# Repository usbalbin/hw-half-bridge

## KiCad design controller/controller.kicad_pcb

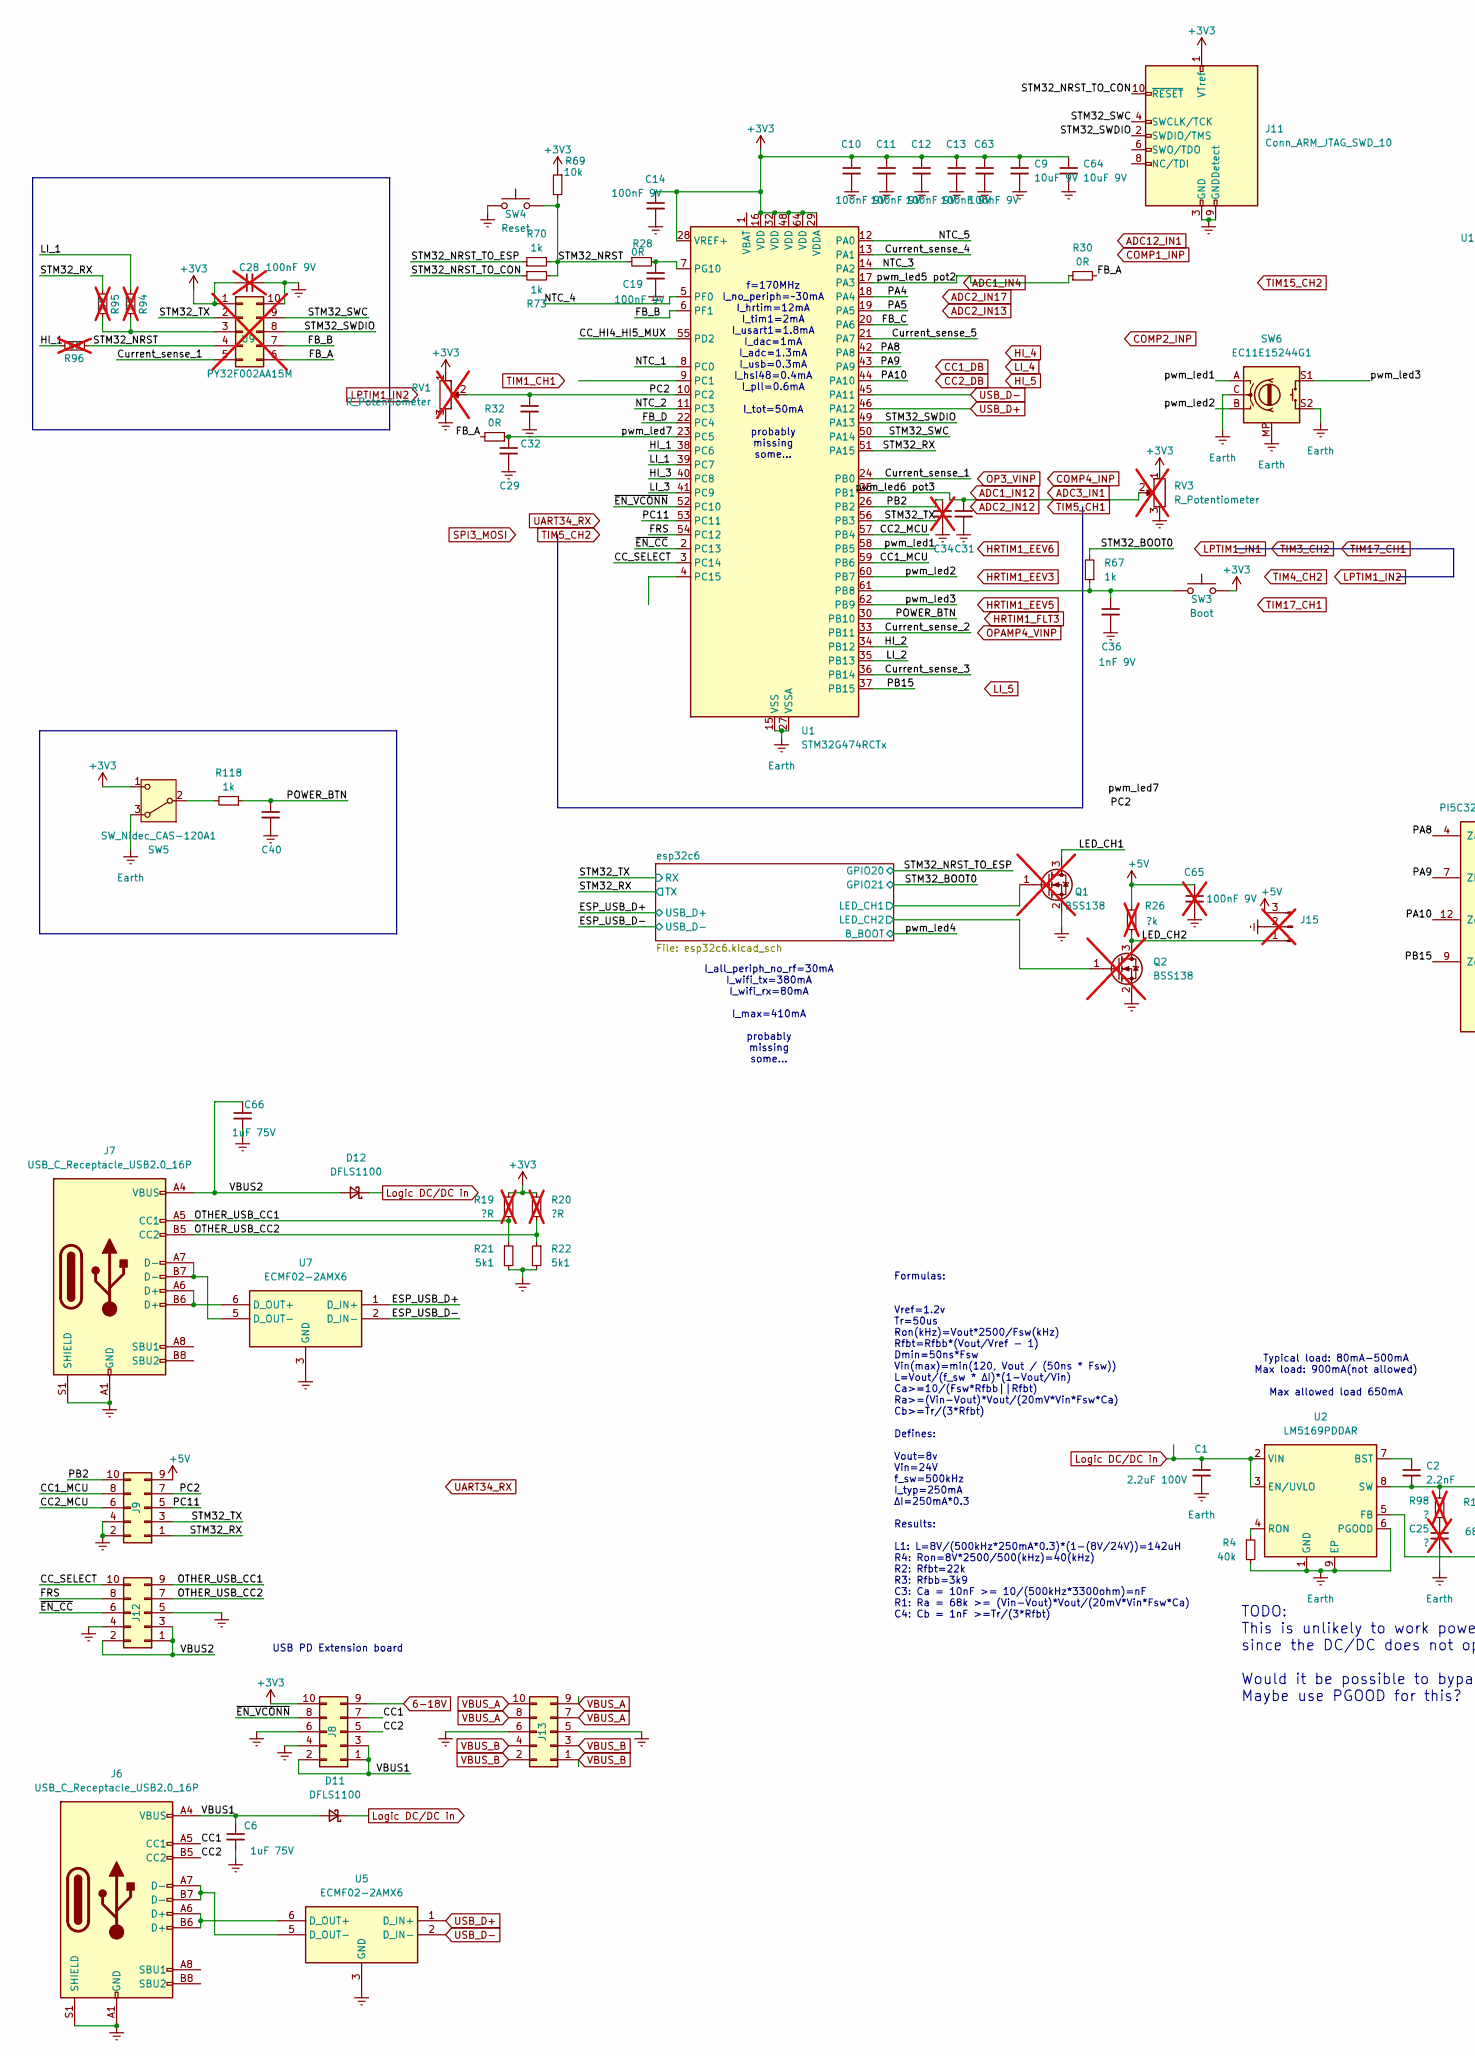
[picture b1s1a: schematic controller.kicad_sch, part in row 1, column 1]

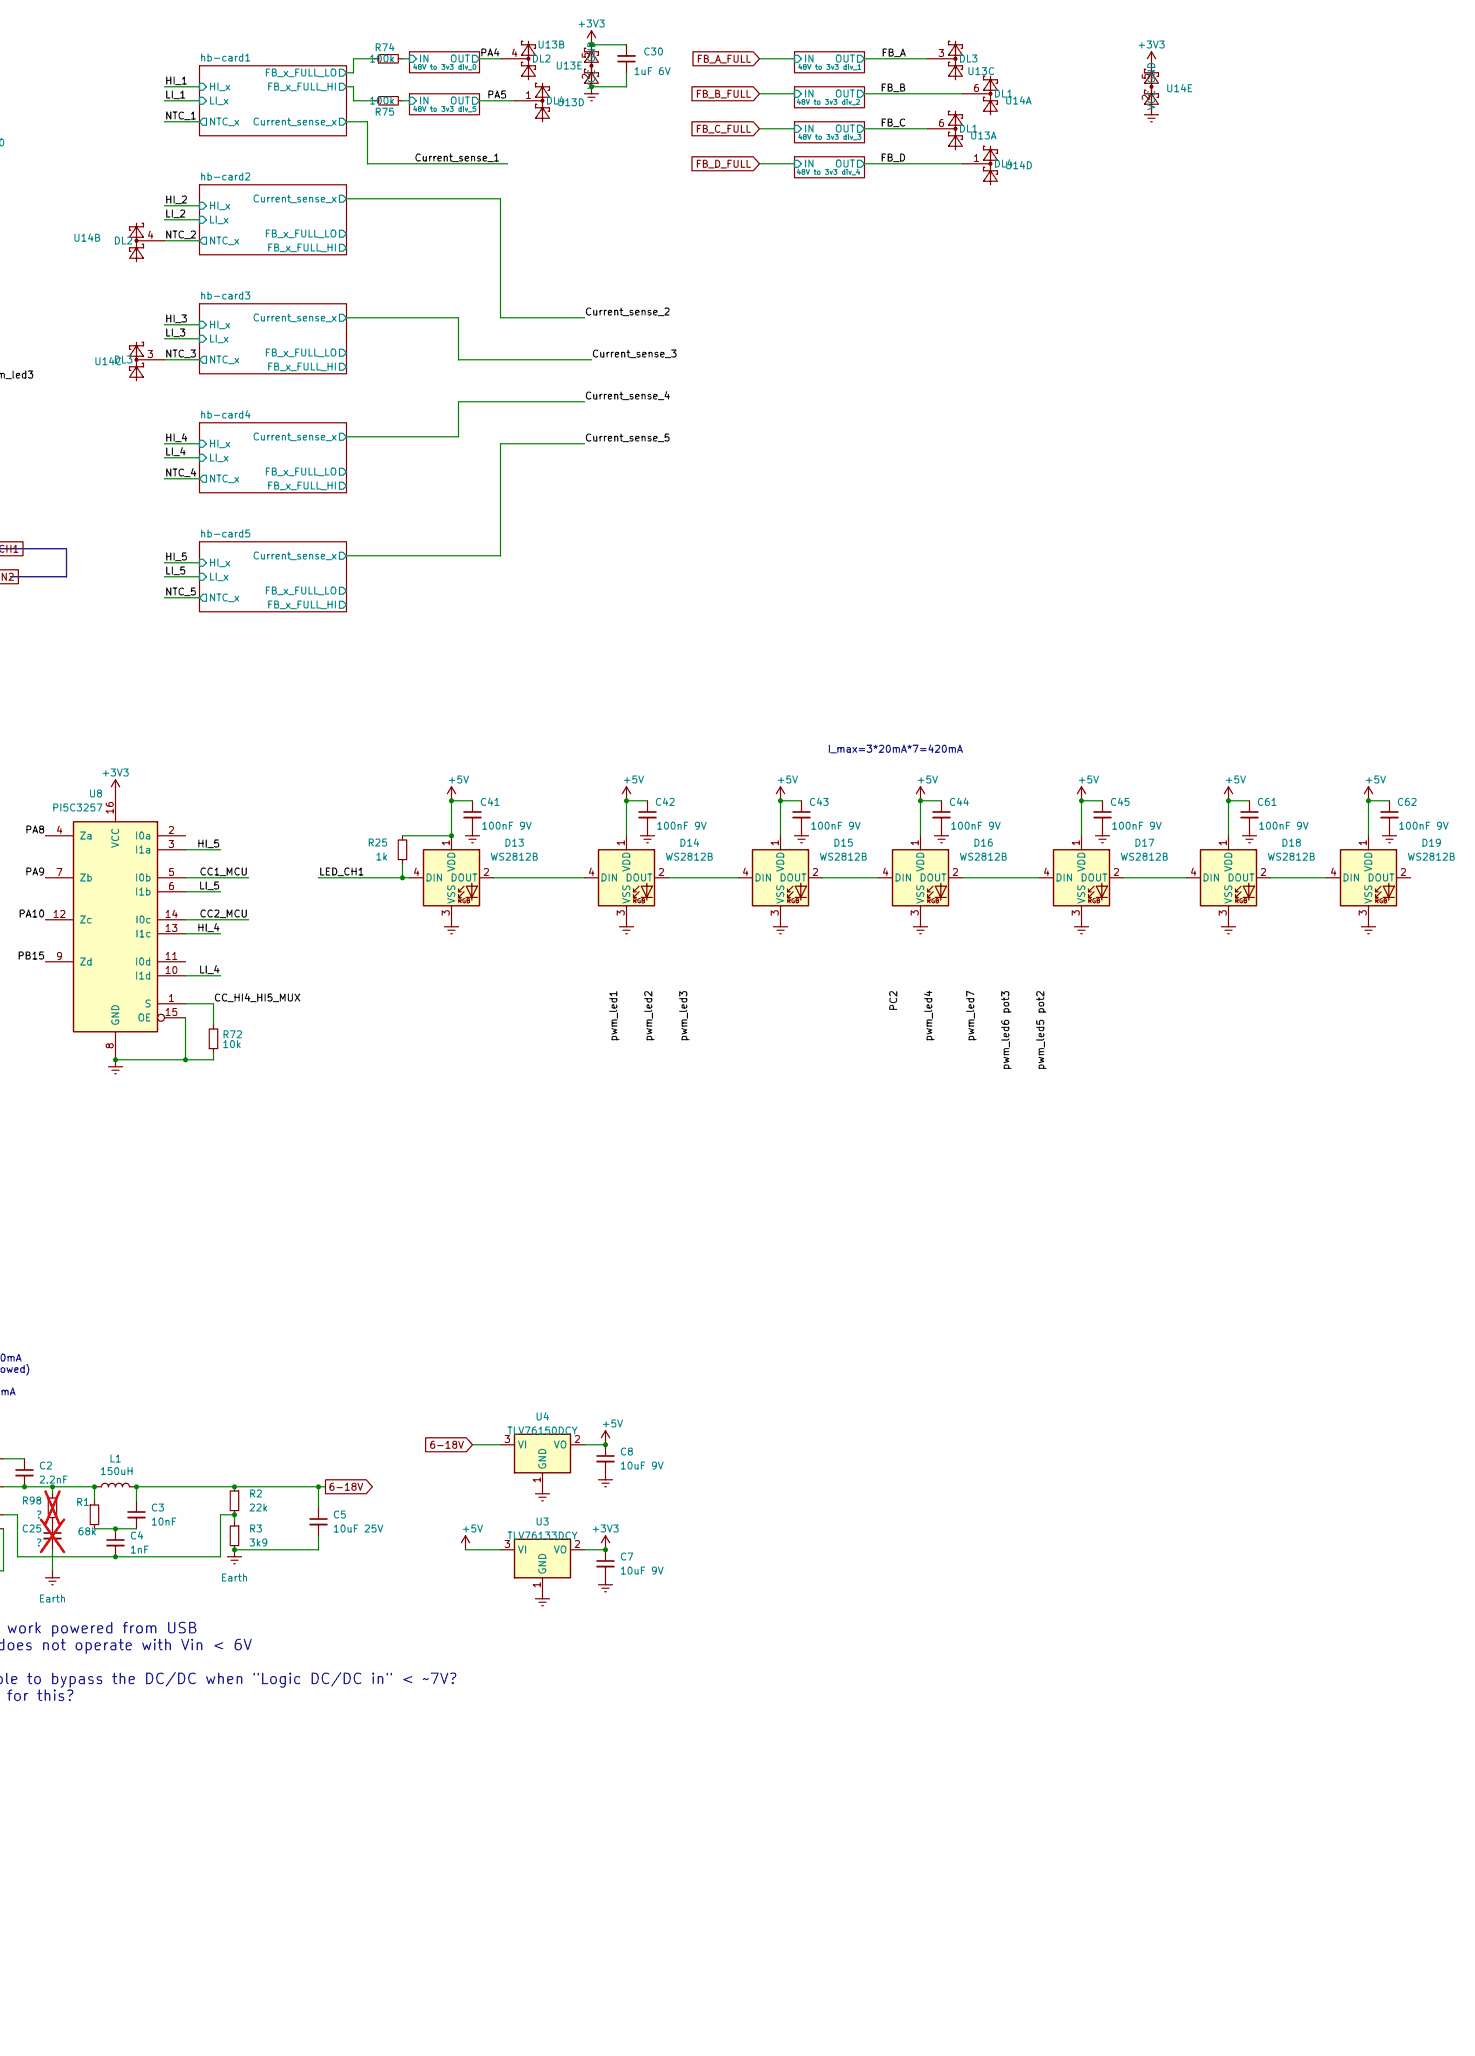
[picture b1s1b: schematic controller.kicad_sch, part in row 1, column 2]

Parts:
C1: 2.2uF 100V; C_1206_3216Metric
C2: 2.2nF; C_0603_1608Metric
C3: 10nF; C_0603_1608Metric
C4: 1nF; C_0603_1608Metric
C5: 10uF 25V; C_1206_3216Metric
C6, C66: 1uF 75V; C_0603_1608Metric
C7, C8, C9, C64: 10uF 9V; C_0805_2012Metric
C10, C11, C12, C13, C14, C19, C29, C31, C32, C40, C41, C42, C43, C44, C45, C61, C62, C63: 100nF 9V; C_0402_1005Metric
C25: ?; C_0603_1608Metric; not fitted
C28, C65: 100nF 9V; C_0402_1005Metric; not fitted
C30: 1uF 6V; C_0402_1005Metric
C34: 10nF 9V; C_0402_1005Metric; not fitted
C36: 1nF 9V; C_0402_1005Metric
D11, D12: DFLS1100; D_PowerDI-123
D13, D14, D15, D16, D17, D18, D19: WS2812B; LED_WS2812B_PLCC4_5.0x5.0mm_P3.2mm; part-num SparkFun Electronics COM-16347
J6, J7: USB_C_Receptacle_USB2.0_16P; USB_C_Receptacle_GCT_USB4105-xx-A_16P_TopMnt_Horizontal; part-num USB4105-GF-A
J8, J9, J11, J12, J13: Conn_ARM_JTAG_SWD_10; PinHeader_2x05_P1.27mm_Vertical_SMD
J15: Conn_01x03_Pin; PinHeader_1x03_P2.54mm_Vertical_SMD_Pin1Left; not fitted
L1: 150uH; L_Murata_LQH55DN_5.7x5.0mm; part-num CLF7045NIT-151M-D
Q1, Q2: BSS138; SOT-23; not fitted
R1: 68k; R_0603_1608Metric
R2: 22k; R_0603_1608Metric
R3: 3k9; R_0603_1608Metric
R4: 40k; R_0603_1608Metric
R19, R20: ?R; R_0402_1005Metric; not fitted
R21, R22: 5k1; R_0402_1005Metric
R25, R67, R70, R73, R118: 1k; R_0402_1005Metric
R26: ?k; R_0402_1005Metric; not fitted
R28: 0R; R_0603_1608Metric
R30, R32: 0R; R_0402_1005Metric
R69, R72: 10k; R_0402_1005Metric
R74, R75: 100k; R_0805_2012Metric
R94, R95, R96: 0R; R_0402_1005Metric; not fitted
R98: ?; R_0603_1608Metric; not fitted
RV1, RV3: R_Potentiometer; Potentiometer_Alps_RK09Y11_Single_Horizontal; not fitted
SW3: Boot; SW_SPST_B3U-1000P; part-num B3U-1000P
SW4: Reset; SW_SPST_B3U-1000P; part-num B3U-1000P
SW5: SW_Nidec_CAS-120A1; SW_Slide_SPDT_Straight_CK_OS102011MS2Q; part-num OS102011MS2QN1C
SW6: EC11E15244G1; RotaryEncoder_Alps_EC11E-Switch_Vertical_H20mm_CircularMoun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; part-num EC11E15244G1
U1: STM32G474RCTx; LQFP-64_10x10mm_P0.5mm
U2: LM5169PDDAR; HSOP-8-1EP_3.9x4.9mm_P1.27mm_EP2.41x3.1mm_ThermalVias; part-num LM5169PDDAR
U3: TLV76133DCY; SOT-223-3_TabPin2; part-num TLV76133DCY
U4: TLV76150DCY; SOT-223-3_TabPin2; part-num TLV76150DCY
U5, U7: ECMF02-2AMX6; ST_UQFN-6L_1.5x1.7mm_P0.5mm; part-num ECMF02-2AMX6
U8: PI5C3257; TQFN-16-1EP_3x3mm_P0.5mm_EP1.6x1.6mm; part-num PI5C3257ZHDEX
U9: PY32F002AA15M; SSOP-10_3.9x4.9mm_P1.00mm; not fitted
U13, U14: QSBT40-7-F; SOT-363_SC-70-6; part-num QSBT40-7-F

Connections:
6-18V: C3.1, C5.1, J8.9, L1.2, R2.1, U4.3 (VI); also elsewhere on the board
+3V3: C7.1, C9.1, C10.1, C11.1, C12.1, C13.1, C14.1, C28.1, C30.2, C63.1, C64.1, J8.10, J11.1 (VTref), R19.1, R20.1, R69.1, RV1.1, RV3.1, SW3.1, SW5.1 (C), U1.16 (VDD), U1.28 (VREF+), U1.29 (VDDA), U1.32 (VDD), U1.48 (VDD), U1.64 (VDD), U3.2 (VO), U8.16 (VCC), U9.1, U13.5 (VCC), U14.5 (VCC); also elsewhere on the board
+5V: C8.1, C41.1, C42.1, C43.1, C44.1, C45.1, C61.1, C62.1, C65.1, D13.1 (VDD), D14.1 (VDD), D15.1 (VDD), D16.1 (VDD), D17.1 (VDD), D18.1 (VDD), D19.1 (VDD), J9.9, J15.3, R25.2, R26.2, U3.3 (VI), U4.2 (VO); also elsewhere on the board
/CC1: J6.A5 (CC1), J8.7
/CC1_MCU: J9.8, U1.59 (PB6), U8.5 (I0b)
/CC2: J6.B5 (CC2), J8.5
/CC2_MCU: J9.6, U1.57 (PB4), U8.14 (I0c)
/CC_HI4_HI5_MUX: R72.2, U1.55 (PD2), U8.1 (S)
/CC_SELECT: J12.10, U1.3 (PC14)
/Current_sense_1: U1.24 (PB0), U9.5; also elsewhere on the board
/Current_sense_2: U1.33 (PB11); also elsewhere on the board
/Current_sense_3: U1.36 (PB14); also elsewhere on the board
/Current_sense_4: U1.13 (PA1); also elsewhere on the board
/Current_sense_5: U1.21 (PA7); also elsewhere on the board
/ESP_USB_D+: U7.1 (D_IN+); also elsewhere on the board
/ESP_USB_D-: U7.2 (D_IN-); also elsewhere on the board
/FRS: J12.8, U1.54 (PC12)
/HI_1: R96.2, U1.38 (PC6); also elsewhere on the board
/HI_2: U1.34 (PB12); also elsewhere on the board
/HI_3: U1.40 (PC8); also elsewhere on the board
/LED_CH1: D13.4 (DIN), Q1.3 (D), R25.1
/LED_CH2: J15.1, Q2.3 (D), R26.1
/LI_1: R94.1, U1.39 (PC7); also elsewhere on the board
/LI_2: U1.35 (PB13); also elsewhere on the board
/LI_3: U1.41 (PC9); also elsewhere on the board
/NTC_1: U1.8 (PC0); also elsewhere on the board
/NTC_2: U1.11 (PC3), U14.4 (DL2); also elsewhere on the board
/NTC_3: U1.14 (PA2), U14.3 (DL3); also elsewhere on the board
/NTC_4: U1.5 (PF0); also elsewhere on the board
/NTC_5: U1.12 (PA0); also elsewhere on the board
/OTHER_USB_CC1: J7.A5 (CC1), J12.9, R19.2, R21.1
/OTHER_USB_CC2: J7.B5 (CC2), J12.7, R20.2, R22.1
/PA4: R74.2, U1.18 (PA4), U13.4 (DL2); also elsewhere on the board
/PA5: R75.2, U1.19 (PA5), U13.1 (DL4); also elsewhere on the board
/PA8: U1.42 (PA8), U8.4 (Za)
/PA9: U1.43 (PA9), U8.7 (Zb)
/PA10: U1.44 (PA10), U8.12 (Zc)
/PB2: C34.1, J9.10, U1.26 (PB2)
/PB15: U1.37 (PB15), U8.9 (Zd)
/PC2: C32.1, J9.7, RV1.2, U1.10 (PC2)
/PC11: J9.5, U1.53 (PC11)
/POWER_BTN: C40.1, R118.1, U1.30 (PB10)
/STM32_BOOT0: R67.2; also elsewhere on the board
/STM32_NRST: R28.1, R69.2, R70.2, R73.2, R96.1, SW4.1, U9.4
/STM32_NRST_TO_CON: J11.10 (~RESET), R73.1
/STM32_NRST_TO_ESP: R70.1; also elsewhere on the board
/STM32_RX: J9.1, R95.1, U1.51 (PA15); also elsewhere on the board
/STM32_SWC: J11.4 (SWCLK/TCK), U1.50 (PA14), U9.9
/STM32_SWDIO: J11.2 (SWDIO/TMS), U1.49 (PA13), U9.8
/STM32_TX: J9.3, U1.56 (PB3), U9.2; also elsewhere on the board
/VBUS1: C6.1, D11.2 (A), J6.A4 (VBUS), J6.A9 (VBUS), J6.B4 (VBUS), J6.B9 (VBUS), J8.1, J8.2, J8.3
/VBUS2: C66.1, D12.2 (A), J7.A4 (VBUS), J7.A9 (VBUS), J7.B4 (VBUS), J7.B9 (VBUS), J12.1, J12.2, J12.3
/esp32c6/LED_CH1: Q1.1 (G); also elsewhere on the board
/esp32c6/LED_CH2: Q2.1 (G); also elsewhere on the board
/hb-card1/FB_x_FULL_HI: R75.1; also elsewhere on the board
/hb-card1/FB_x_FULL_LO: R74.1; also elsewhere on the board
/pwm_led1: SW6.A, U1.58 (PB5)
/pwm_led2: SW6.B, U1.60 (PB7)
/pwm_led3: SW6.S1, U1.62 (PB9)
/pwm_led5 pot2: R30.1, U1.17 (PA3)
/pwm_led6 pot3: C31.1, RV3.2, U1.25 (PB1)
/pwm_led7: C29.1, R32.1, U1.23 (PC5)
/~EN_CC: J12.6, U1.2 (PC13)
/~EN_VCONN: J8.8, U1.52 (PC10)
Earth: C1.2, C5.2, C6.2, C7.2, C8.2, C9.2, C10.2, C11.2, C12.2, C13.2, C14.2, C19.2, C25.2, C28.2, C29.2, C30.1, C31.2, C32.2, C34.2, C36.2, C40.2, C41.2, C42.2, C43.2, C44.2, C45.2, C61.2, C62.2, C63.2, C64.2, C65.2, C66.2, D13.3 (VSS), D14.3 (VSS), D15.3 (VSS), D16.3 (VSS), D17.3 (VSS), D18.3 (VSS), D19.3 (VSS), J6.A1 (GND), J6.A12 (GND), J6.B1 (GND), J6.B12 (GND), J6.S1 (SHIELD), J7.A1 (GND), J7.A12 (GND), J7.B1 (GND), J7.B12 (GND), J7.S1 (SHIELD), J8.4, J8.6, J9.2, J9.4, J11.3 (GND), J11.5 (GND), J11.9 (GNDDetect), J12.4, J12.5, J13.5, J13.6, J15.2, Q1.2 (S), Q2.2 (S), R3.2, R4.2, R21.2, R22.2, R72.1, RV1.3, RV3.3, SW4.2, SW5.3 (A), SW6.C, SW6.MP, SW6.S2, U1.15 (VSS), U1.27 (VSSA), U1.31 (VSS), U1.47 (VSS), U1.63 (VSS), U2.1 (GND), U2.6 (PGOOD), U2.9 (EP), U3.1 (GND), U4.1 (GND), U5.3 (GND), U5.4 (NC), U7.3 (GND), U7.4 (NC), U8.8 (GND), U8.15 (OE), U9.10, U13.2 (GND), U14.2 (GND); also elsewhere on the board
FB_A_FULL: R30.2, R32.2, U9.6, U13.3 (DL3); also elsewhere on the board
FB_B_FULL: U1.6 (PF1), U9.7, U14.6 (DL1); also elsewhere on the board
FB_C_FULL: U1.20 (PA6), U13.6 (DL1); also elsewhere on the board
FB_D_FULL: U1.22 (PC4), U14.1 (DL4); also elsewhere on the board
HI_4: U8.13 (I1c); also elsewhere on the board
HI_5: U8.3 (I1a); also elsewhere on the board
LI_4: U8.10 (I1d); also elsewhere on the board
LI_5: U8.6 (I1b); also elsewhere on the board
Logic DC/DC in: C1.1, D11.1 (K), D12.1 (K), U2.2 (VIN), U2.3 (EN/UVLO); also elsewhere on the board
unnamed: C3.2, C4.1, R1.2
unnamed: C25.1, R98.2
unnamed: D13.2 (DOUT), D14.4 (DIN)
unnamed: D14.2 (DOUT), D15.4 (DIN)
unnamed: D15.2 (DOUT), D16.4 (DIN)
unnamed: D16.2 (DOUT), D17.4 (DIN)
unnamed: D17.2 (DOUT), D18.4 (DIN)
unnamed: D18.2 (DOUT), D19.4 (DIN)
unnamed: R118.2, SW5.2 (B)
unnamed: C36.1, R67.1, SW3.2, U1.61 (PB8)
unnamed: C19.1, R28.2, U1.7 (PG10)
unnamed: C2.1, U2.7 (BST)
unnamed: C4.2, R2.2, R3.1, U2.5 (FB)
unnamed: R4.1, U2.4 (RON)
unnamed: C2.2, L1.1, R1.1, R98.1, U2.8 (SW)
unnamed: J6.A6 (D+), J6.B6 (D+), U5.6 (D_OUT+)
unnamed: J6.A7 (D-), J6.B7 (D-), U5.5 (D_OUT-)
unnamed: J7.A6 (D+), J7.B6 (D+), U7.6 (D_OUT+)
unnamed: J7.A7 (D-), J7.B7 (D-), U7.5 (D_OUT-)
unnamed: R94.2, R95.2, U9.3
USB_D+: U1.46 (PA12), U5.1 (D_IN+)
USB_D-: U1.45 (PA11), U5.2 (D_IN-)
VBUS_A: J13.7, J13.8, J13.9, J13.10; also elsewhere on the board
VBUS_B: J13.1, J13.2, J13.3, J13.4; also elsewhere on the board

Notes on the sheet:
Typical load: 80mA-500mA Max load: 900mA(not allowed) Max allowed load 650mA
I_all_periph_no_rf=30mA I_wifi_tx=380mA I_wifi_rx=80mA I_max=410mA probably missing some...
I_max=3*20mA*7=420mA
USB PD Extension board
f=170MHz I_no_periph=~30mA I_hrtim=12mA I_tim1=2mA I_usart1=1.8mA I_dac=1mA I_adc=1.3mA I_usb=0.3mA I_hsi48=0.4mA I_pll=0.6mA I_tot=50mA probably missing some...
Formulas: Vref=1.2v Tr=50us Ron(kHz)=Vout*2500/Fsw(kHz) Rfbt=Rfbb*(Vout/Vref - 1) Dmin=50ns*Fsw Vin(max)=min(120, Vout / (50ns * Fsw)) L=Vout/(f_sw * ΔI)*(1-Vout/Vin) Ca>=10/(Fsw*Rfbb||Rfbt) Ra>=(Vin-Vout)*Vout/(20mV*Vin*Fsw*Ca) Cb>=Tr/(3*Rfbt) Defines: Vout=8v Vin=24V f_sw=500kHz I_typ=250mA ΔI=25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
TODO: This is unlikely to work powered from USB since the DC/DC does not operate with Vin < 6V Would it be possible to bypass the DC/DC when "Logic DC/DC in" < ~7V? Maybe use PGOOD for this?

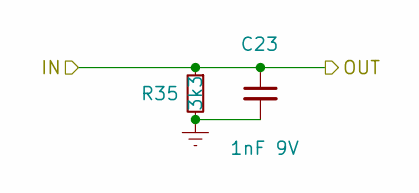
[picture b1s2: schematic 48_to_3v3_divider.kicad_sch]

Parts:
C23: 1nF 9V; C_0402_1005Metric
R35: 3k3; R_0402_1005Metric

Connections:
Earth: C23.2, R35.2; also elsewhere on the board
FB_D_FULL: C23.1, R35.1; also elsewhere on the board

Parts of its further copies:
C21, C22, C24, C26, C27: 1nF 9V; C_0402_1005Metric
R27, R31, R39, R78, R82: 3k3; R_0402_1005Metric

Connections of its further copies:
/PA4: C24.1, R39.1; also elsewhere on the board
/PA5: C27.1, R82.1; also elsewhere on the board
Earth: C21.2, C22.2, C24.2, C26.2, C27.2, R27.2, R31.2, R39.2, R78.2, R82.2; also elsewhere on the board
FB_A_FULL: C26.1, R78.1; also elsewhere on the board
FB_B_FULL: C21.1, R27.1; also elsewhere on the board
FB_C_FULL: C22.1, R31.1; also elsewhere on the board

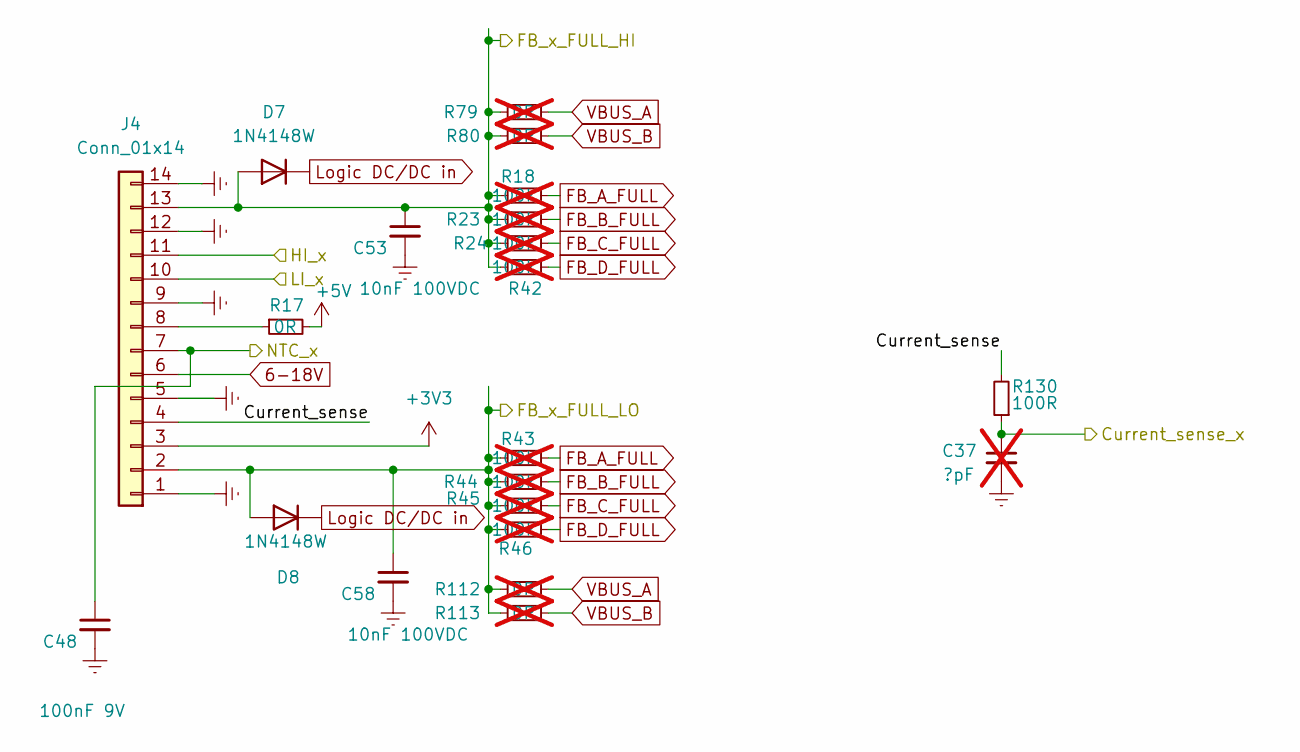
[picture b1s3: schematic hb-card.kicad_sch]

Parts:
C37: ?pF; C_0402_1005Metric; not fitted
C48: 100nF 9V; C_0402_1005Metric
C53, C58: 10nF 100VDC; C_0603_1608Metric
D7, D8: 1N4148W; D_SOD-123
J4: Conn_01x14; half_bridge_card
R17: 0R; R_0402_1005Metric
R18, R23, R24, R42, R43, R44, R45, R46: 100k; R_0805_2012Metric; not fitted
R79, R80, R112, R113: 0R; R_0805_2012Metric; not fitted
R130: 100R; R_0402_1005Metric

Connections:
6-18V: J4.6; also elsewhere on the board
+3V3: J4.3; also elsewhere on the board
+5V: R17.2; also elsewhere on the board
/Current_sense_4: C37.1, R130.1; also elsewhere on the board
/NTC_4: C48.1, J4.7; also elsewhere on the board
/hb-card4/Current_sense: J4.4, R130.2
/hb-card4/FB_x_FULL_HI: C53.1, D7.2 (A), J4.13, R18.1, R23.1, R24.1, R42.1, R79.1, R80.1
/hb-card4/FB_x_FULL_LO: C58.1, D8.2 (A), J4.2, R43.1, R44.1, R45.1, R46.1, R112.1, R113.1
Earth: C37.2, C48.2, C53.2, C58.2, J4.1, J4.5, J4.9, J4.12, J4.14; also elsewhere on the board
FB_A_FULL: R18.2, R43.2; also elsewhere on the board
FB_B_FULL: R23.2, R44.2; also elsewhere on the board
FB_C_FULL: R24.2, R45.2; also elsewhere on the board
FB_D_FULL: R42.2, R46.2; also elsewhere on the board
HI_4: J4.11; also elsewhere on the board
LI_4: J4.10; also elsewhere on the board
Logic DC/DC in: D7.1 (K), D8.1 (K); also elsewhere on the board
unnamed: J4.8, R17.1
VBUS_A: R79.2, R112.2; also elsewhere on the board
VBUS_B: R80.2, R113.2; also elsewhere on the board

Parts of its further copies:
C33, C35, C38, C39: ?pF; C_0402_1005Metric; not fitted
C46, C47, C49, C50: 100nF 9V; C_0402_1005Metric
C51, C52, C54, C55, C56, C57, C59, C60: 10nF 100VDC; C_0603_1608Metric
D1, D2, D3, D4, D5, D6, D9, D10: 1N4148W; D_SOD-123
J1, J2, J3, J5: Conn_01x14; half_bridge_card
R5, R51, R84, R90: 0R; R_0402_1005Metric
R6, R8, R9, R13, R14, R15, R16, R41, R52, R53, R54, R55, R56, R61, R62, R63, R86, R87, R88, R89, R91, R92, R93, R99, R100, R101, R102, R103, R104, R105, R106, R107: 100k; R_0805_2012Metric; not fitted
R68, R71, R76, R77, R81, R83, R85, R97, R108, R109, R110, R111, R114, R115, R116, R117: 0R; R_0805_2012Metric; not fitted
R122, R128, R132, R134: 100R; R_0402_1005Metric

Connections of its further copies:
6-18V: J1.6, J2.6, J3.6, J5.6; also elsewhere on the board
+3V3: J1.3, J2.3, J3.3, J5.3; also elsewhere on the board
+5V: R5.2, R51.2, R84.2, R90.2; also elsewhere on the board
/Current_sense_1: C33.1, R122.1; also elsewhere on the board
/Current_sense_2: C39.1, R134.1; also elsewhere on the board
/Current_sense_3: C35.1, R128.1; also elsewhere on the board
/Current_sense_5: C38.1, R132.1; also elsewhere on the board
/HI_1: J1.11; also elsewhere on the board
/HI_2: J2.11; also elsewhere on the board
/HI_3: J3.11; also elsewhere on the board
/LI_1: J1.10; also elsewhere on the board
/LI_2: J2.10; also elsewhere on the board
/LI_3: J3.10; also elsewhere on the board
/NTC_1: C46.1, J1.7; also elsewhere on the board
/NTC_2: C50.1, J2.7; also elsewhere on the board
/NTC_3: C47.1, J3.7; also elsewhere on the board
/NTC_5: C49.1, J5.7; also elsewhere on the board
/hb-card1/Current_sense: J1.4, R122.2
/hb-card1/FB_x_FULL_HI: C51.1, D1.2 (A), J1.13, R68.1, R71.1, R86.1, R87.1, R88.1, R89.1; also elsewhere on the board
/hb-card1/FB_x_FULL_LO: C56.1, D2.2 (A), J1.2, R91.1, R92.1, R93.1, R99.1, R108.1, R109.1; also elsewhere on the board
/hb-card2/Current_sense: J2.4, R134.2
/hb-card2/FB_x_FULL_HI: C55.1, D3.2 (A), J2.13, R85.1, R97.1, R100.1, R101.1, R102.1, R103.1
/hb-card2/FB_x_FULL_LO: C60.1, D4.2 (A), J2.2, R104.1, R105.1, R106.1, R107.1, R116.1, R117.1
/hb-card3/Current_sense: J3.4, R128.2
/hb-card3/FB_x_FULL_HI: C52.1, D5.2 (A), J3.13, R6.1, R8.1, R9.1, R13.1, R76.1, R77.1
/hb-card3/FB_x_FULL_LO: C57.1, D6.2 (A), J3.2, R14.1, R15.1, R16.1, R41.1, R110.1, R111.1
/hb-card5/Current_sense: J5.4, R132.2
/hb-card5/FB_x_FULL_HI: C54.1, D9.2 (A), J5.13, R52.1, R53.1, R54.1, R55.1, R81.1, R83.1
/hb-card5/FB_x_FULL_LO: C59.1, D10.2 (A), J5.2, R56.1, R61.1, R62.1, R63.1, R114.1, R115.1
Earth: C33.2, C35.2, C38.2, C39.2, C46.2, C47.2, C49.2, C50.2, C51.2, C52.2, C54.2, C55.2, C56.2, C57.2, C59.2, C60.2, J1.1, J1.5, J1.9, J1.12, J1.14, J2.1, J2.5, J2.9, J2.12, J2.14, J3.1, J3.5, J3.9, J3.12, J3.14, J5.1, J5.5, J5.9, J5.12, J5.14; also elsewhere on the board
FB_A_FULL: R6.2, R14.2, R52.2, R56.2, R86.2, R91.2, R100.2, R104.2; also elsewhere on the board
FB_B_FULL: R8.2, R15.2, R53.2, R61.2, R87.2, R92.2, R101.2, R105.2; also elsewhere on the board
FB_C_FULL: R9.2, R16.2, R54.2, R62.2, R88.2, R93.2, R102.2, R106.2; also elsewhere on the board
FB_D_FULL: R13.2, R41.2, R55.2, R63.2, R89.2, R99.2, R103.2, R107.2; also elsewhere on the board
HI_5: J5.11; also elsewhere on the board
LI_5: J5.10; also elsewhere on the board
Logic DC/DC in: D1.1 (K), D2.1 (K), D3.1 (K), D4.1 (K), D5.1 (K), D6.1 (K), D9.1 (K), D10.1 (K); also elsewhere on the board
unnamed: J1.8, R84.1
unnamed: J2.8, R90.1
unnamed: J3.8, R5.1
unnamed: J5.8, R51.1
VBUS_A: R68.2, R76.2, R81.2, R85.2, R108.2, R110.2, R114.2, R116.2; also elsewhere on the board
VBUS_B: R71.2, R77.2, R83.2, R97.2, R109.2, R111.2, R115.2, R117.2; also elsewhere on the board

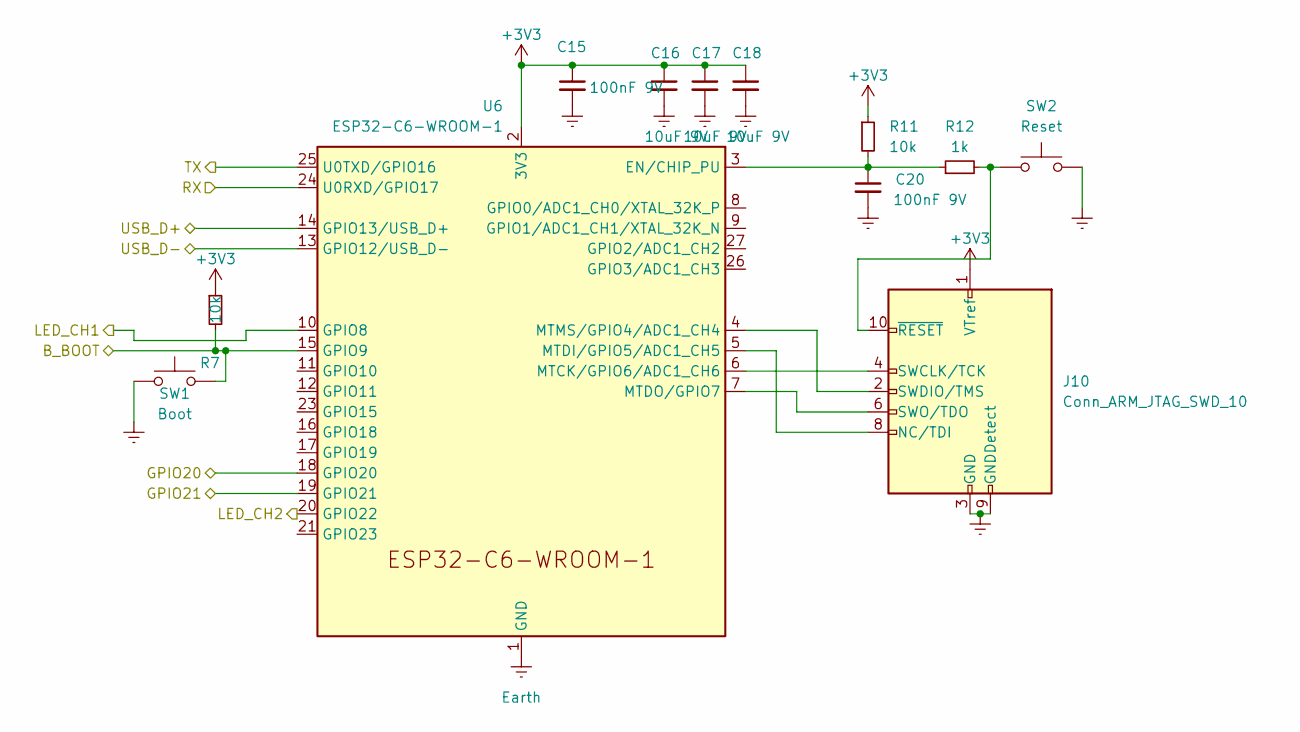
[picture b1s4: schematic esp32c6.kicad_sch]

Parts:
C15, C20: 100nF 9V; C_0402_1005Metric
C16, C17, C18: 10uF 9V; C_0805_2012Metric
J10: Conn_ARM_JTAG_SWD_10; PinHeader_2x05_P1.27mm_Vertical_SMD
R7: 10k; R_0603_1608Metric
R11: 10k; R_0402_1005Metric
R12: 1k; R_0603_1608Metric
SW1: Boot; SW_SPST_B3U-1000P; part-num B3U-1000P
SW2: Reset; SW_SPST_B3U-1000P; part-num B3U-1000P
U6: ESP32-C6-WROOM-1; part-num ESP32-C6-WROOM-1

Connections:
+3V3: C15.1, C16.1, C17.1, C18.1, J10.1 (VTref), R7.1, R11.1, U6.2 (3V3); also elsewhere on the board
/ESP_USB_D+: U6.14 (GPIO13/USB_D+); also elsewhere on the board
/ESP_USB_D-: U6.13 (GPIO12/USB_D-); also elsewhere on the board
/STM32_BOOT0: U6.19 (GPIO21); also elsewhere on the board
/STM32_NRST_TO_ESP: U6.18 (GPIO20); also elsewhere on the board
/STM32_RX: U6.25 (U0TXD/GPIO16); also elsewhere on the board
/STM32_TX: U6.24 (U0RXD/GPIO17); also elsewhere on the board
/esp32c6/LED_CH1: U6.10 (GPIO8); also elsewhere on the board
/esp32c6/LED_CH2: U6.20 (GPIO22); also elsewhere on the board
/pwm_led4: R7.2, SW1.1, U6.15 (GPIO9)
Earth: C15.2, C16.2, C17.2, C18.2, C20.2, J10.3 (GND), J10.5 (GND), J10.9 (GNDDetect), SW1.2, SW2.2, U6.1 (GND), U6.28 (GND), U6.29 (GND); also elsewhere on the board
unnamed: J10.8 (NC/TDI), U6.5 (MTDI/GPIO5/ADC1_CH5)
unnamed: J10.4 (SWCLK/TCK), U6.6 (MTCK/GPIO6/ADC1_CH6)
unnamed: J10.2 (SWDIO/TMS), U6.4 (MTMS/GPIO4/ADC1_CH4)
unnamed: J10.6 (SWO/TDO), U6.7 (MTDO/GPIO7)
unnamed: J10.10 (~RESET), R12.2, SW2.1
unnamed: C20.1, R11.2, R12.1, U6.3 (EN/CHIP_PU)

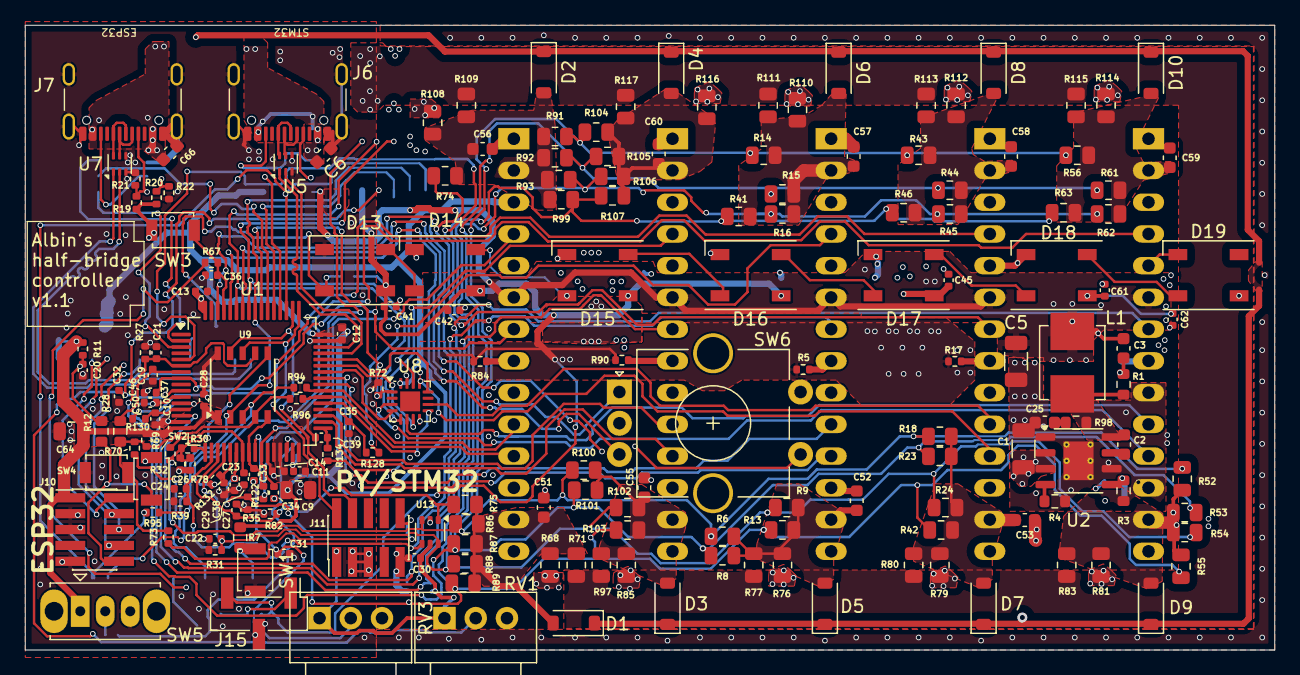
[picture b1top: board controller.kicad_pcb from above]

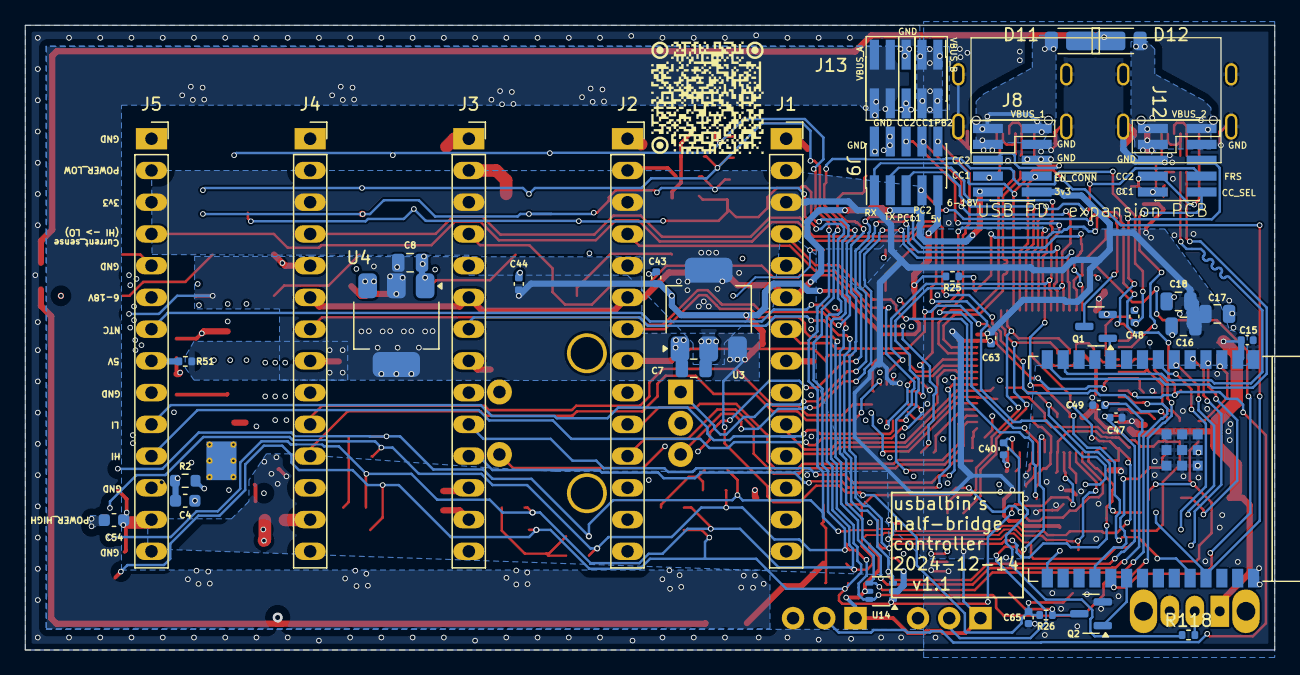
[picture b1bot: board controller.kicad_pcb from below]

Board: 4 copper layers, 100.0 x 50.0 mm, 225 parts (38 on the bottom side), 123 nets.
